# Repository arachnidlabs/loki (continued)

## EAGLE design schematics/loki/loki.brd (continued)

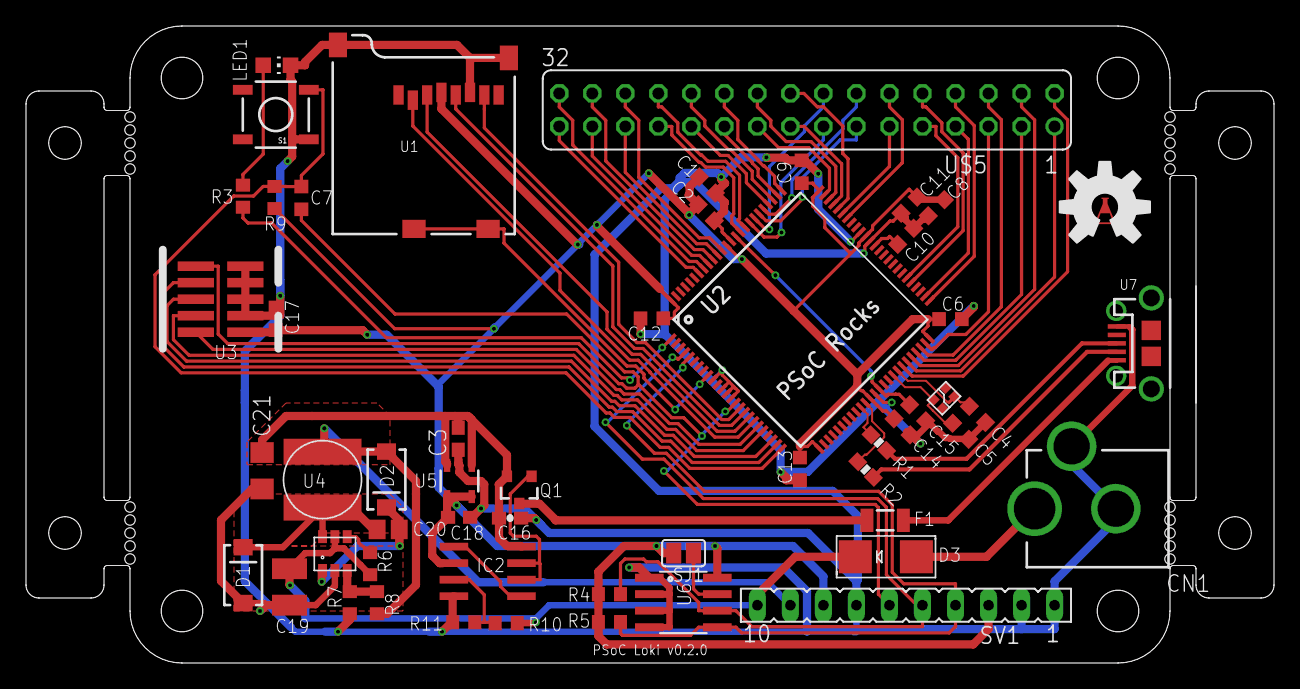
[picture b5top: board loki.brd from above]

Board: 2 copper layers, 96.0 x 49.0 mm, 57 parts (1 on the bottom side), 72 nets.

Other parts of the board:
U$1: ARACHNID_LABS_LOGO_SM
U$6: LOKI_LOGO
U$12: OSHW-LOGO-L

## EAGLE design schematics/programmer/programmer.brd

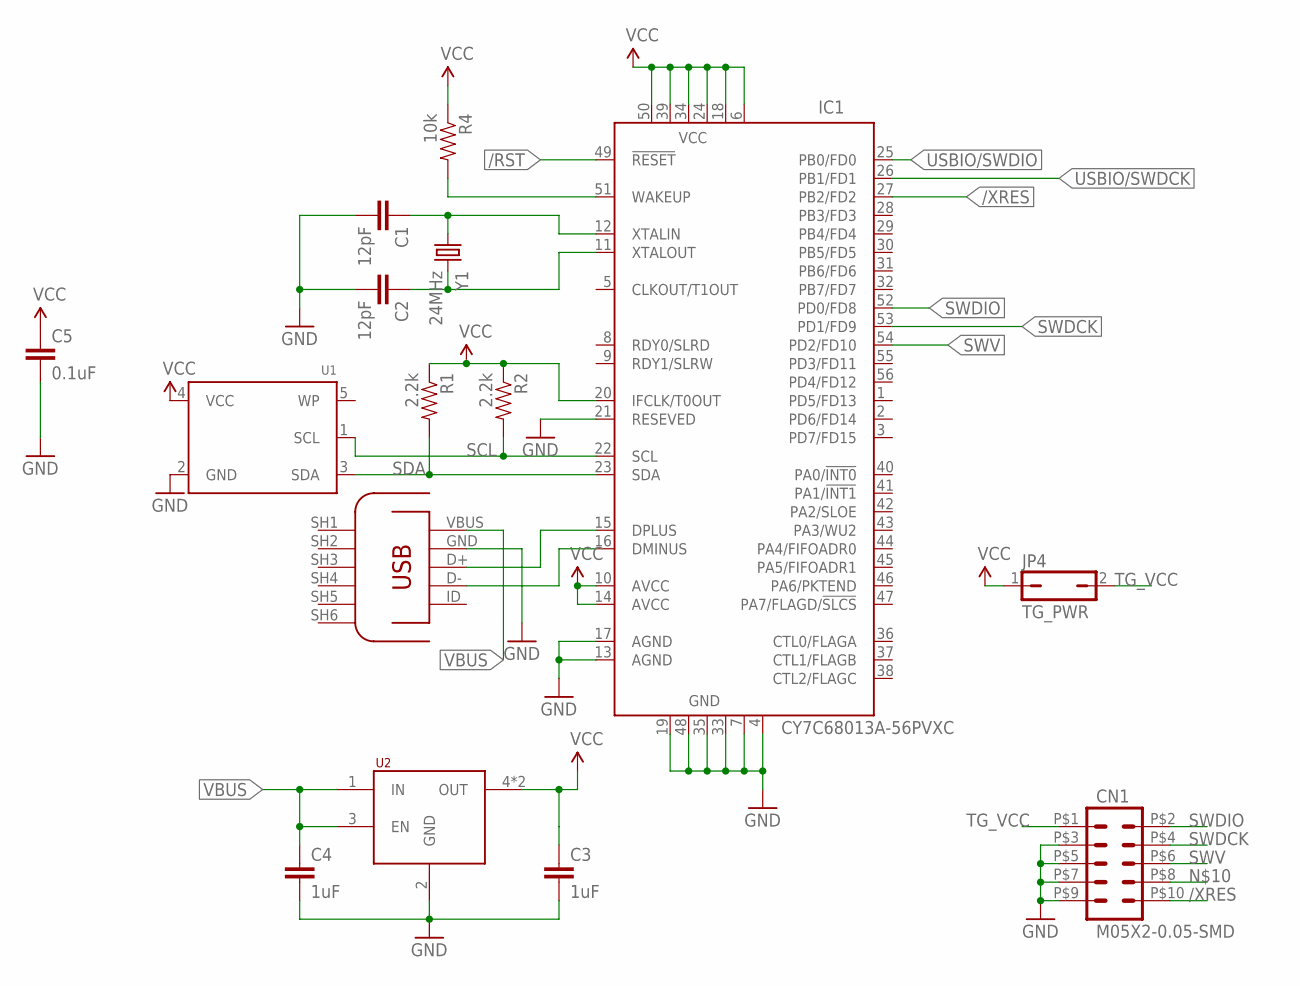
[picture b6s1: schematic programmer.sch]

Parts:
C1, C2: 12pF; 0805
C3, C4: 1uF; 0805
C5: 0.1uF; 0805
CN1: M05X2-0.05-SMD; PINHD-2X5-0.05-SMD
IC1: CY7C68013A-56PVXC; SSOP56
JP4: TG_PWR; JP1
R1, R2: 2.2k; 0805
R4: 10k; 0805
U1: EEPROM_I2C_MCP24AA32; SOT23-5
U2: TLV702XX; SOT23-5
U$3: MICROUSB; USB-MICROB
Y1: 24MHz; XRCGB-XTAL

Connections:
/RST: IC1.49 (!RESET)
/XRES: CN1.P$10 (10), IC1.27 (PB2/FD2)
GND: C1.2, C2.2, C3.2, C4.2, C5.2, CN1.P$3 (3), CN1.P$5 (5), CN1.P$7 (7), CN1.P$9 (9), IC1.4 (GND), IC1.7 (GND), IC1.13 (AGND), IC1.17 (AGND), IC1.19 (GND), IC1.21 (RESEVED), IC1.33 (GND), IC1.35 (GND), IC1.48 (GND), U1.2 (GND), U2.2 (GND), U$3.GND
unnamed: IC1.16 (DMINUS), U$3.D-
unnamed: IC1.15 (DPLUS), U$3.D+
unnamed: IC1.51 (WAKEUP), R4.2
SCL: IC1.22 (SCL), R2.2, U1.1 (SCL)
SDA: IC1.23 (SDA), R1.2, U1.3 (SDA)
SWDCK: CN1.P$4 (4), IC1.53 (PD1/FD9)
SWDIO: CN1.P$2 (2), IC1.52 (PD0/FD8)
SWV: CN1.P$6 (6), IC1.54 (PD2/FD10)
TG_VCC: CN1.P$1 (1), JP4.2
USBIO/SWDCK: IC1.26 (PB1/FD1)
USBIO/SWDIO: IC1.25 (PB0/FD0)
VBUS: C4.1, U2.1 (IN), U2.3 (EN), U$3.VBUS (VCC)
VCC: C3.1, C5.1, IC1.6 (VCC), IC1.10 (AVCC), IC1.14 (AVCC), IC1.18 (VCC), IC1.20 (IFCLK/T0OUT), IC1.24 (VCC), IC1.34 (VCC), IC1.39 (VCC), IC1.50 (VCC), JP4.1, R1.1, R2.1, R4.1, U1.4 (VCC), U2.4 (OUT), U2.5 (OUT)
XTALIN: C1.1, IC1.12 (XTALIN), Y1.1
XTALOUT: C2.1, IC1.11 (XTALOUT), Y1.2

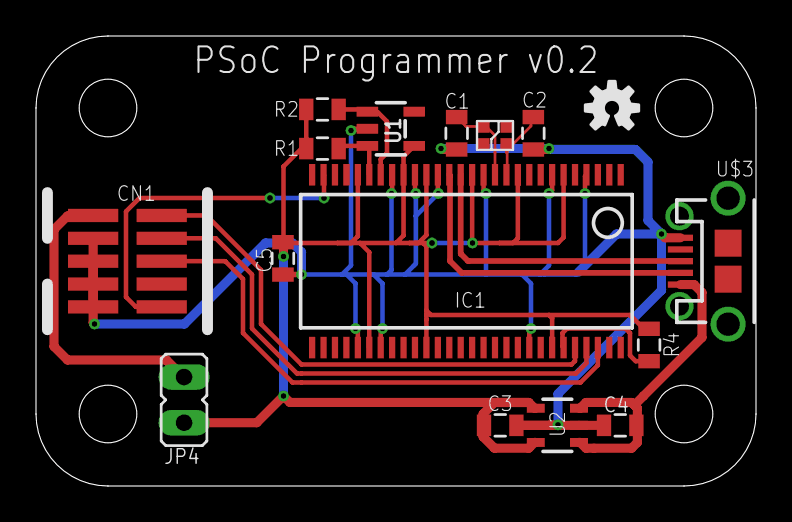
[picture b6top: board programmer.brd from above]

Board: 2 copper layers, 40.0 x 25.0 mm, 16 parts (0 on the bottom side), 15 nets.

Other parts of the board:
U$1: OSHW-LOGO-S

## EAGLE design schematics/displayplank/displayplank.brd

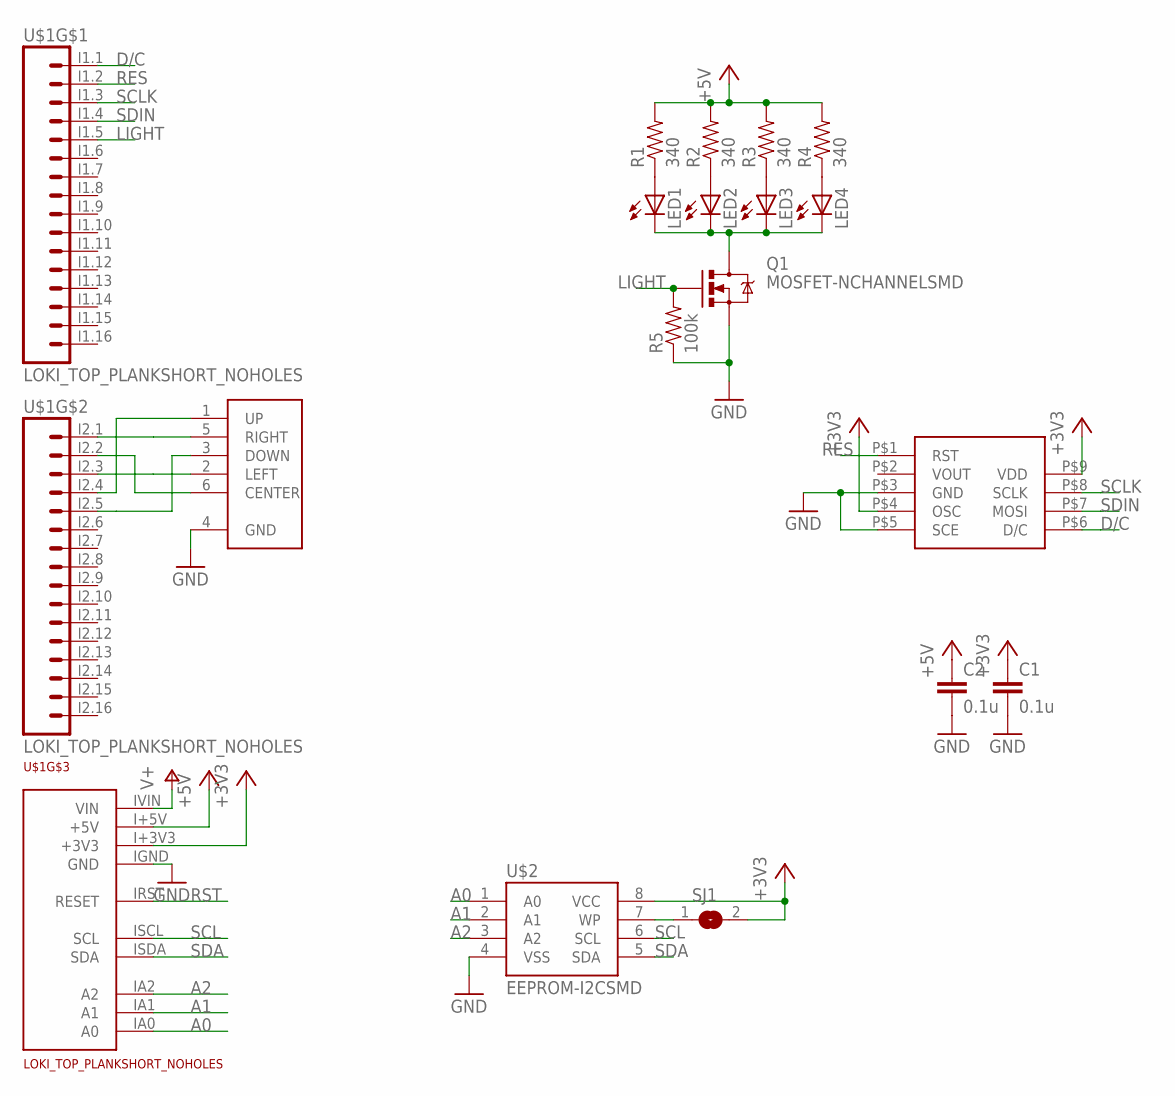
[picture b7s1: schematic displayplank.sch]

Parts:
C1, C2: 0.1u; 0805
LED1, LED2, LED3, LED4: LEDSML0805; SML0805
Q1: MOSFET-NCHANNELSMD; SOT23-3
R1, R2, R3, R4: 340; 0805
R5: 100k; 0805
SJ1: SJ
U$1: LOKI_TOP_PLANKSHORT_NOHOLES; TOP_PLANK_SHORT_NOHOLES
U$2: EEPROM-I2CSMD; SO08
U$3: JOYSTICK-10MM
U$5: 5110-SCREEN

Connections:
+3V3: C1.1, SJ1.2, U$1.I+3V3 (+3V3), U$2.8 (VCC), U$5.P$4 (OSC), U$5.P$9 (VDD)
+5V: C2.1, R1.2, R2.2, R3.2, R4.2, U$1.I+5V (+5V)
A0: U$1.IA0 (A0), U$2.1 (A0)
A1: U$1.IA1 (A1), U$2.2 (A1)
A2: U$1.IA2 (A2), U$2.3 (A2)
D/C: U$1.I1.1 (1), U$5.P$6 (D/C)
GND: C1.2, C2.2, Q1.2 (S), R5.1, U$1.IGND (GND), U$2.4 (VSS), U$3.4 (GND), U$5.P$3 (GND), U$5.P$5 (SCE)
LIGHT: Q1.1 (G), R5.2, U$1.I1.5 (5)
unnamed: SJ1.1, U$2.7 (WP)
unnamed: LED1.A, R1.1
unnamed: LED2.A, R2.1
unnamed: LED3.A, R3.1
unnamed: LED4.A, R4.1
unnamed: LED1.C, LED2.C, LED3.C, LED4.C, Q1.3 (D)
unnamed: U$1.I2.4 (4), U$3.1 (UP)
unnamed: U$1.I2.2 (2), U$3.6 (CENTER)
unnamed: U$1.I2.3 (3), U$3.2 (LEFT)
unnamed: U$1.I2.5 (5), U$3.3 (DOWN)
unnamed: U$1.I2.1 (1), U$3.5 (RIGHT)
RES: U$1.I1.2 (2), U$5.P$1 (RST)
RST: U$1.IRST (RESET)
SCL: U$1.ISCL (SCL), U$2.6 (SCL)
SCLK: U$1.I1.3 (3), U$5.P$8 (SCLK)
SDA: U$1.ISDA (SDA), U$2.5 (SDA)
SDIN: U$1.I1.4 (4), U$5.P$7 (MOSI)
V+: U$1.IVIN (VIN)

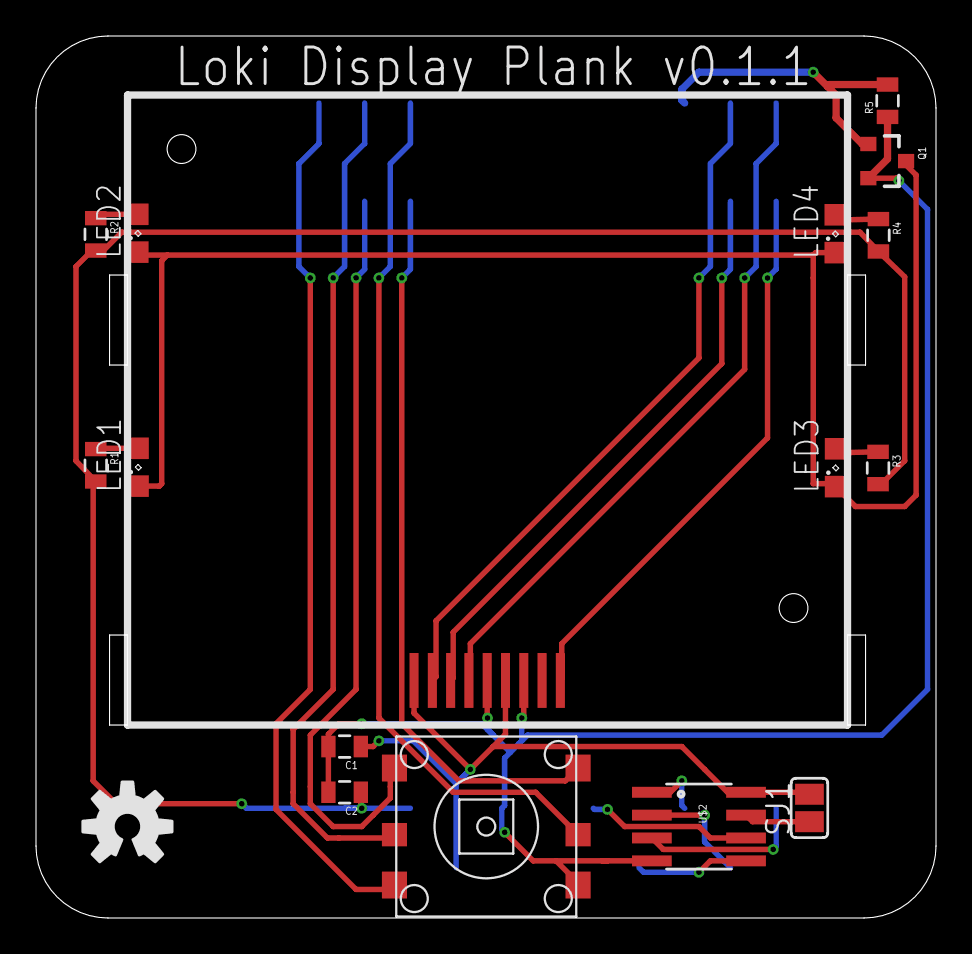
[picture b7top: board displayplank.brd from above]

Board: 2 copper layers, 50.0 x 49.0 mm, 18 parts (0 on the bottom side), 24 nets.

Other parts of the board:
U$4: OSHW-LOGO-M

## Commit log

2012-11-27 Gitignore for Eagle temporary files.
2012-11-29 Minor layout changes; improvements to 2 pin plank template.
2012-11-29 Added reverse polarity protection diode.
2012-11-30 Added top planks to the Eagle library.
2012-11-30 Added protoplank and 8 pin plank template.
2012-12-01 Updated protoplank to use square pads for ease of SMT soldering.
2012-12-01 Added decoupling capacitors to the protoboard.
2012-12-01 Added first revision of motor plank, 6 pin plank template.
2012-12-01 Added schematics and drawings for motor plank.
2012-12-01 Text should be on a text layer, not in copper.
2012-12-01 Add LED indicators for motor outputs.
2012-12-01 Increase isolation on top ground plane.
2012-12-01 Move capacitors to the side closer to ground.
2012-12-02 Added display plank; top plank sample.
2012-12-02 Replace usb mini connector with usb micro one.
2012-12-02 Widened a few traces where possible.
2012-12-02 Added tripads for edge connectors on protoshield.
2012-12-02 Minor positioning tweak.
2012-12-02 Updated images.
2012-12-02 Reorganized repository.
2012-12-03 Tweaks to planks; change 0604 parts for 0805 where possible
    Also added 4 pin plank; minor text changes.
2012-12-05 Misc tweaks, generated gerbers.
2012-12-06 Added soundplank.
2012-12-07 Improved soundplank labelling; generated gerbers.
2012-12-09 Updated soundplank to make use of opamp outputs when on the bottom.
2012-12-10 Fix footprints on the soundplank so they're not backwards (oops!)
2012-12-13 Updated loki stencil
2012-12-16 Improve audio routing for line out.
2012-12-23 Displayplank: Added pulldown for FET, improved capacitor spacing, fixed layer of name text.
2012-12-29 Reworked Loki to fit the 100TQFP package.
2012-12-29 Misc fixes.
2012-12-31 Misc layout improvements to Loki; updated to v0.2.
2013-01-01 Added schematic for PSoC programmer.
2013-01-01 Added missing board file from previous commit.
2013-01-01 Added missing gerbers and loki schematic
2013-01-05 Fixed both Loki and the programmer to use 3.3v for power on programming headers.
2013-01-13 Layout tweaks to motor plank.
2013-01-27 Implemented bootloader host.
2013-01-27 Fix write protect pullups on plank EEPROMs.
2013-01-27 Updated loki and plank names when they change.
2013-01-27 Separate LokiInfo from protocol level details.
2013-01-27 Remove unnecessary bootloader delay.
2013-01-31 Added first demo app (game of life) and library code for the Nokia display.
2013-01-31 Added basic readme.
2013-02-02 Add short delay when writing EEPROM data to allow the EEPROM to finish.
2013-02-02 Work on constant current plank.
2013-02-03 Minor library changes, initial commit of Snake project.
2013-02-03 New files in Snake project
2013-02-03 Rework of current plank, now using opamp and trimpot to set current limit.
2013-02-03 Thermal vias etc for current plank.
2013-02-03 Moar symmetry!
2013-02-04 Updates to current plank silkscreen etc.
2013-02-04 Minor work on snake demo
2013-02-10 Added logo to Current Plank, generated gerbers.
2013-02-10 Created new Shield Plank.
2013-02-10 Updated Loki library with Arachnid Labs logo.
2013-02-10 Updated layout image.
2013-02-10 Added ground pour; regenerated gerbers; generated images.
2013-02-10 Refactored the EEPROM layout to fit in 256 bytes; minor other UI improvements.
2013-02-10 Retitled edit plank info form.
2013-02-12 Fixed top right corner missing in board outline
2013-04-08 Changes to firmware loader, including load/dump option for eeproms.
2013-04-08 Tweaks to shield and current planks.
2013-04-08 EEPROM data for Loki and planks.
